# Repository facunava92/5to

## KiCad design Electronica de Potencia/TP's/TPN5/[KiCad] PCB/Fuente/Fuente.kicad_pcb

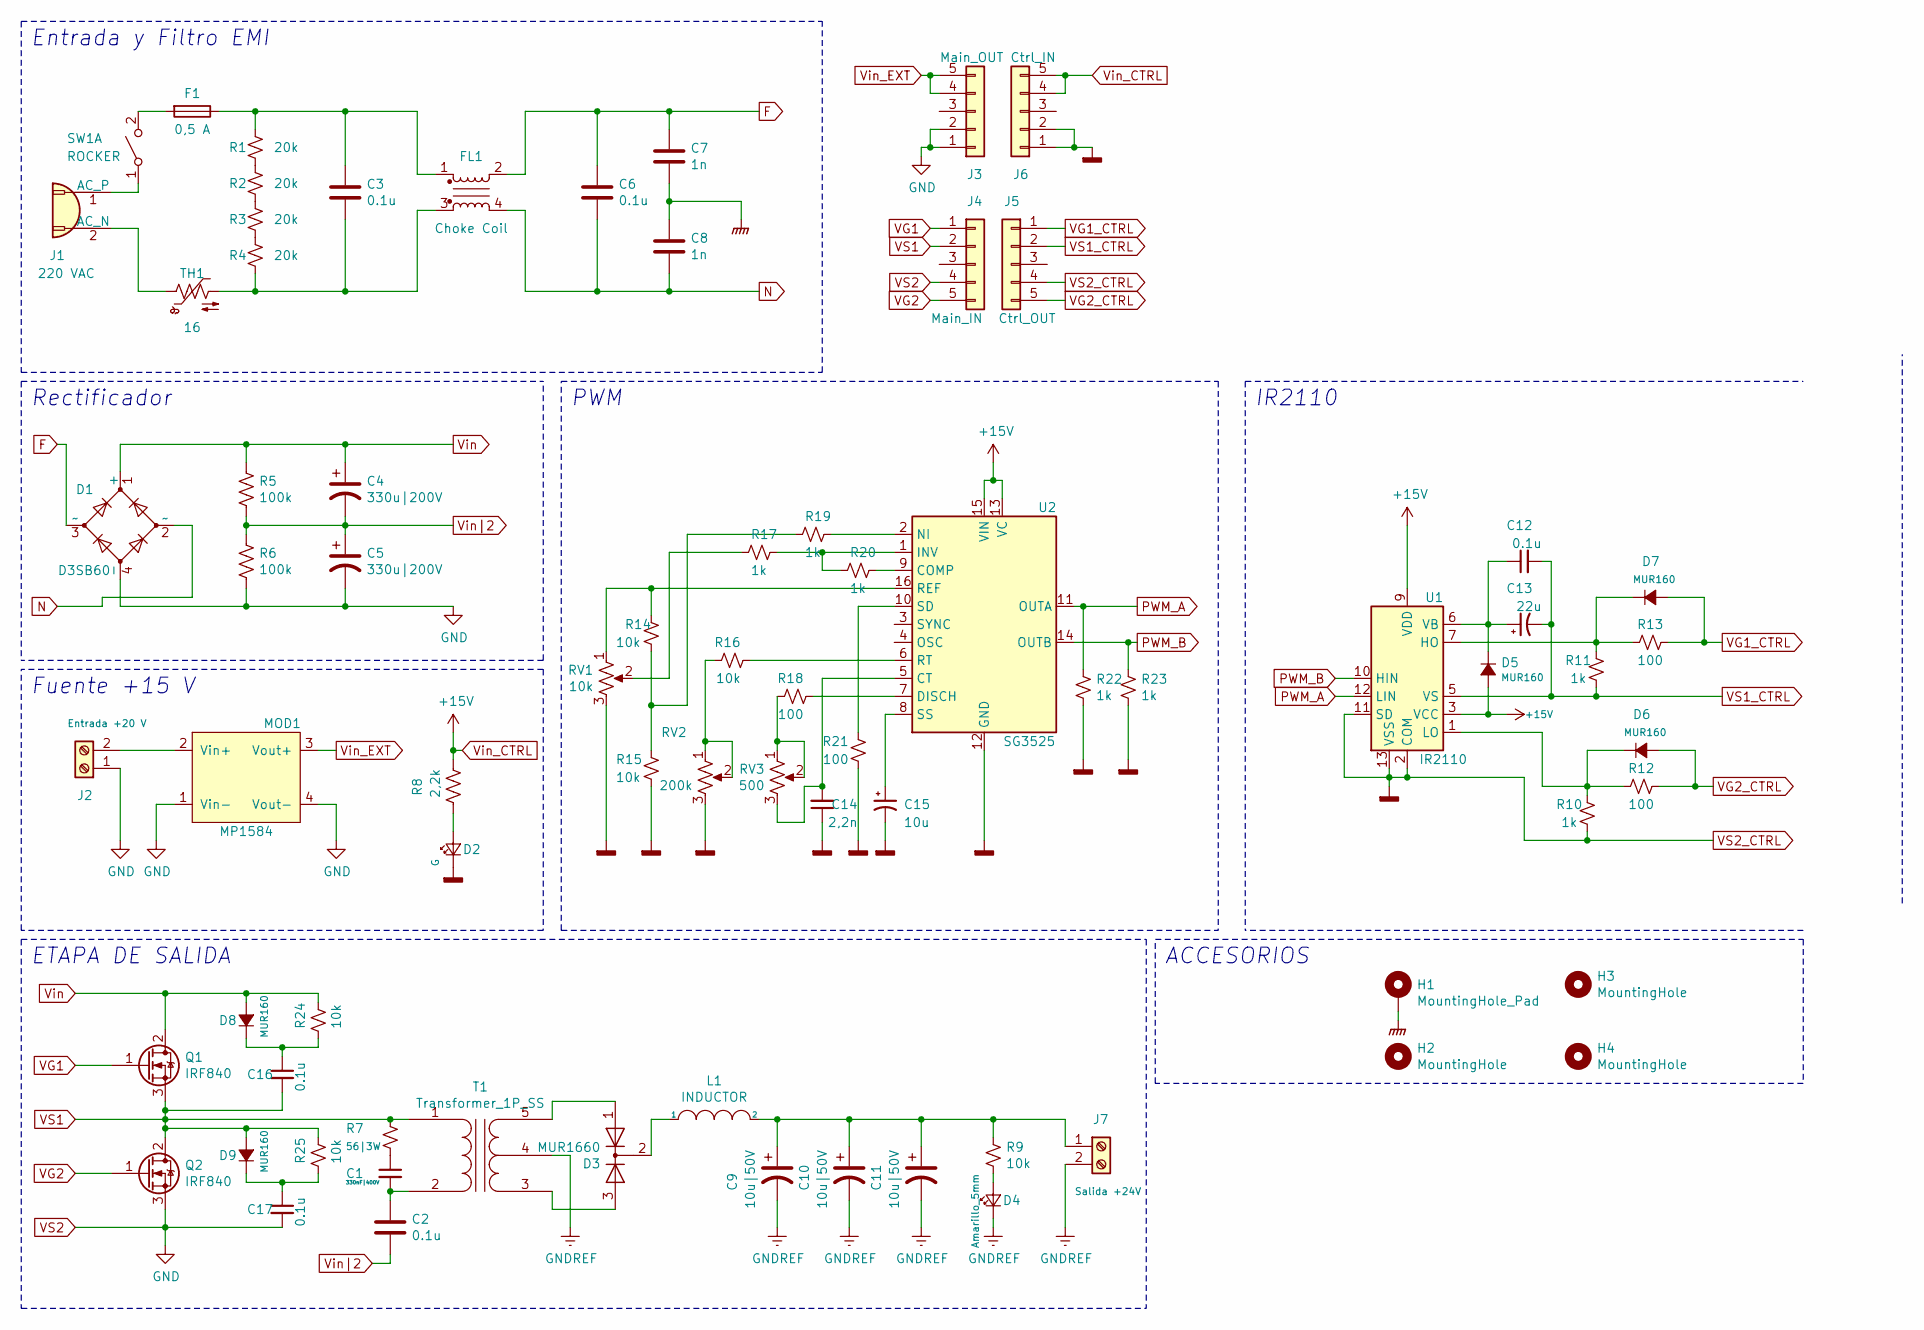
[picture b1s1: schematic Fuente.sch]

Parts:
C1: 330nF|400V; C_Rect_L16.5mm_W5.0mm_P15.00mm_MKT
C2, C3, C6: 0.1u; C_Rect_L16.5mm_W5.0mm_P15.00mm_MKT
C4, C5: 330u|200V; CP_Radial_D25.0mm_P10.00mm_SnapIn
C7, C8: 1n; C_EMI
C9, C10, C11: 10u|50V; CP_Radial_D5.0mm_P2.50mm
C12, C16, C17: 0.1u; C_Disc_D3.8mm_W2.6mm_P2.50mm
C13: 22u; CP_Radial_D5.0mm_P2.50mm
C14: 2,2n; C_Disc_D3.8mm_W2.6mm_P2.50mm
C15: 10u; CP_Radial_D5.0mm_P2.50mm
D1: D3SB60; DS3B
D2: G; LED_D5.0mm_Clear
D3: MUR1660; TO-220-3_Vertical
D4: Amarillo_5mm; LED_D5.0mm_Clear
D5, D6, D7, D8, D9: MUR160; D_DO-41_SOD81_P10.16mm_Horizontal
F1: 0,5 A; Fuse_4pin_A
FL1: Choke Coil; Choke_A
H1: MountingHole_Pad; MountingHole_3.2mm_M3_DIN965_Pad
H2, H3, H4: MountingHole; MountingHole_3.2mm_M3_DIN965
J1: 220 VAC; IEC-C8
J2: Entrada +20 V; TerminalBlock_bornier-2_P5.08mm
J3: Main_OUT; PinSocket_1x05_P2.54mm_Vertical
J4: Main_IN; PinSocket_1x05_P2.54mm_Vertical
J5: Ctrl_OUT; PinHeader_1x05_P2.54mm_Vertical
J6: Ctrl_IN; PinHeader_1x05_P2.54mm_Vertical
J7: Salida +24V; TerminalBlock_bornier-2_P5.08mm
L1: INDUCTOR; L_Toroid_Vertical_L22.4mm_W10.2mm_P7.90mm_Vishay_TJ4
MOD1: MP1584
Q1, Q2: IRF840; TO-220-3_Vertical
R1, R2, R3, R4: 20k; R_0805_2012Metric_Pad1.15x1.40mm_HandSolder
R5, R6: 100k; R_Axial_DIN0207_L6.3mm_D2.5mm_P10.16mm_Horizontal
R7: 56|3W; R_Axial_DIN0617_L17.0mm_D6.0mm_P20.32mm_Horizontal
R8: 2,2k; R_Axial_DIN0207_L6.3mm_D2.5mm_P10.16mm_Horizontal
R9, R14, R15, R16, R24, R25: 10k; R_Axial_DIN0207_L6.3mm_D2.5mm_P10.16mm_Horizontal
R10, R11, R17, R19, R20, R22, R23: 1k; R_Axial_DIN0207_L6.3mm_D2.5mm_P10.16mm_Horizontal
R12, R13, R21: 100; R_Axial_DIN0207_L6.3mm_D2.5mm_P10.16mm_Horizontal
R18: 100; R_Axial_DIN0204_L3.6mm_D1.6mm_P5.08mm_Horizontal
RV1: 10k; Potentiometer_Bourns_3266Y_Vertical
RV2: 200k; Potentiometer_Bourns_3266Y_Vertical
RV3: 500; Potentiometer_Bourns_3266Y_Vertical
SW1: ROCKER; Rocker
T1: Transformer_1P_SS; Transformador_EE25
TH1: 16; NTC-16
U1: IR2110; DIP-14_W7.62mm_LongPads
U2: SG3525; DIP-16_W7.62mm_LongPads

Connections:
F: C6.1, C7.1, D1.3 (~~), FL1.2
GNDPWR: C7.2, C8.1, H1.1
GNDREF: C9.2, C10.2, C11.2, D4.1 (K), J7.2, T1.4 (SC)
N: C6.2, C8.2, D1.2 (~~), FL1.4
unnamed: C1.1, R7.2
unnamed: C1.2, C2.1, T1.2 (AB)
unnamed: C3.1, F1.1, FL1.1, R1.1
unnamed: C3.2, FL1.3, R4.2, TH1.2
unnamed: C9.1, C10.1, C11.1, J7.1, L1.2, R9.1
unnamed: C12.1, C13.1, D5.1 (K), U1.6 (VB)
unnamed: C14.2, RV3.3, U2.5 (CT)
unnamed: C15.1, U2.8 (SS)
unnamed: C16.1, D8.1 (K), R24.2
unnamed: C17.1, D9.1 (K), R25.2
unnamed: D2.2 (A), R8.1
unnamed: D3.1 (A), T1.5 (SB)
unnamed: D3.2 (K), L1.1
unnamed: D3.3 (A), T1.3 (SA)
unnamed: D4.2 (A), R9.2
unnamed: D6.1 (K), R10.2, R12.1, U1.1 (LO)
unnamed: D7.1 (K), R11.2, R13.1, U1.7 (HO)
unnamed: F1.2, SW1.2 (B)
unnamed: J1.1 (AC_P), SW1.1 (A)
unnamed: J1.2 (AC_N), TH1.1
unnamed: J2.2, MOD1.2 (Vin+)
unnamed: R1.2, R2.1
unnamed: R2.2, R3.1
unnamed: R3.2, R4.1
unnamed: R14.1, RV1.1, U2.16 (REF)
unnamed: R14.2, R15.1, R19.2
unnamed: R16.1, RV2.1, RV2.2
unnamed: R16.2, U2.6 (RT)
unnamed: R17.1, R20.2, U2.1 (INV)
unnamed: R17.2, RV1.2
unnamed: R18.1, RV3.1, RV3.2
unnamed: R18.2, U2.7 (DISCH)
unnamed: R19.1, U2.2 (NI)
unnamed: R20.1, U2.9 (COMP)
unnamed: R21.2, U2.10 (SD)
PWM_A: R22.1, U1.12 (LIN), U2.11 (OUTA)
PWM_B: R23.1, U1.10 (HIN), U2.14 (OUTB)
VG1: J4.1, Q1.1 (G)
VG1_CTRL: D7.2 (A), J5.1, R13.2
VG2: J4.5, Q2.1 (G)
VG2_CTRL: D6.2 (A), J5.5, R12.2
VS1: C16.2, D9.2 (A), J4.2, Q1.3 (S), Q2.2 (D), R7.1, R25.1, T1.1 (AA)
VS1_CTRL: C12.2, C13.2, J5.2, R11.1, U1.5 (VS)
VS2: C5.2, C17.2, D1.4 (-), J2.1, J3.1, J3.2, J4.4, MOD1.1 (Vin-), MOD1.4 (Vout-), Q2.3 (S), R6.2
VS2_CTRL: C14.1, C15.2, D2.1 (K), J5.4, J6.1, J6.2, R10.1, R15.2, R21.1, R22.2, R23.2, RV1.3, RV2.3, U1.2 (COM), U1.11 (SD), U1.13 (VSS), U2.12 (GND)
Vin: C4.1, D1.1 (+), D8.2 (A), Q1.2 (D), R5.1, R24.1
Vin_CTRL: D5.2 (A), J6.4, J6.5, R8.2, U1.3 (VCC), U1.9 (VDD), U2.13 (VC), U2.15 (VIN)
Vin_EXT: J3.4, J3.5, MOD1.3 (Vout+)
Vin|2: C2.2, C4.2, C5.1, R5.2, R6.1

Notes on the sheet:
Entrada y Filtro EMI
Rectificador
Fuente +15 V
PWM
IR2110
ETAPA DE SALIDA
ACCESORIOS

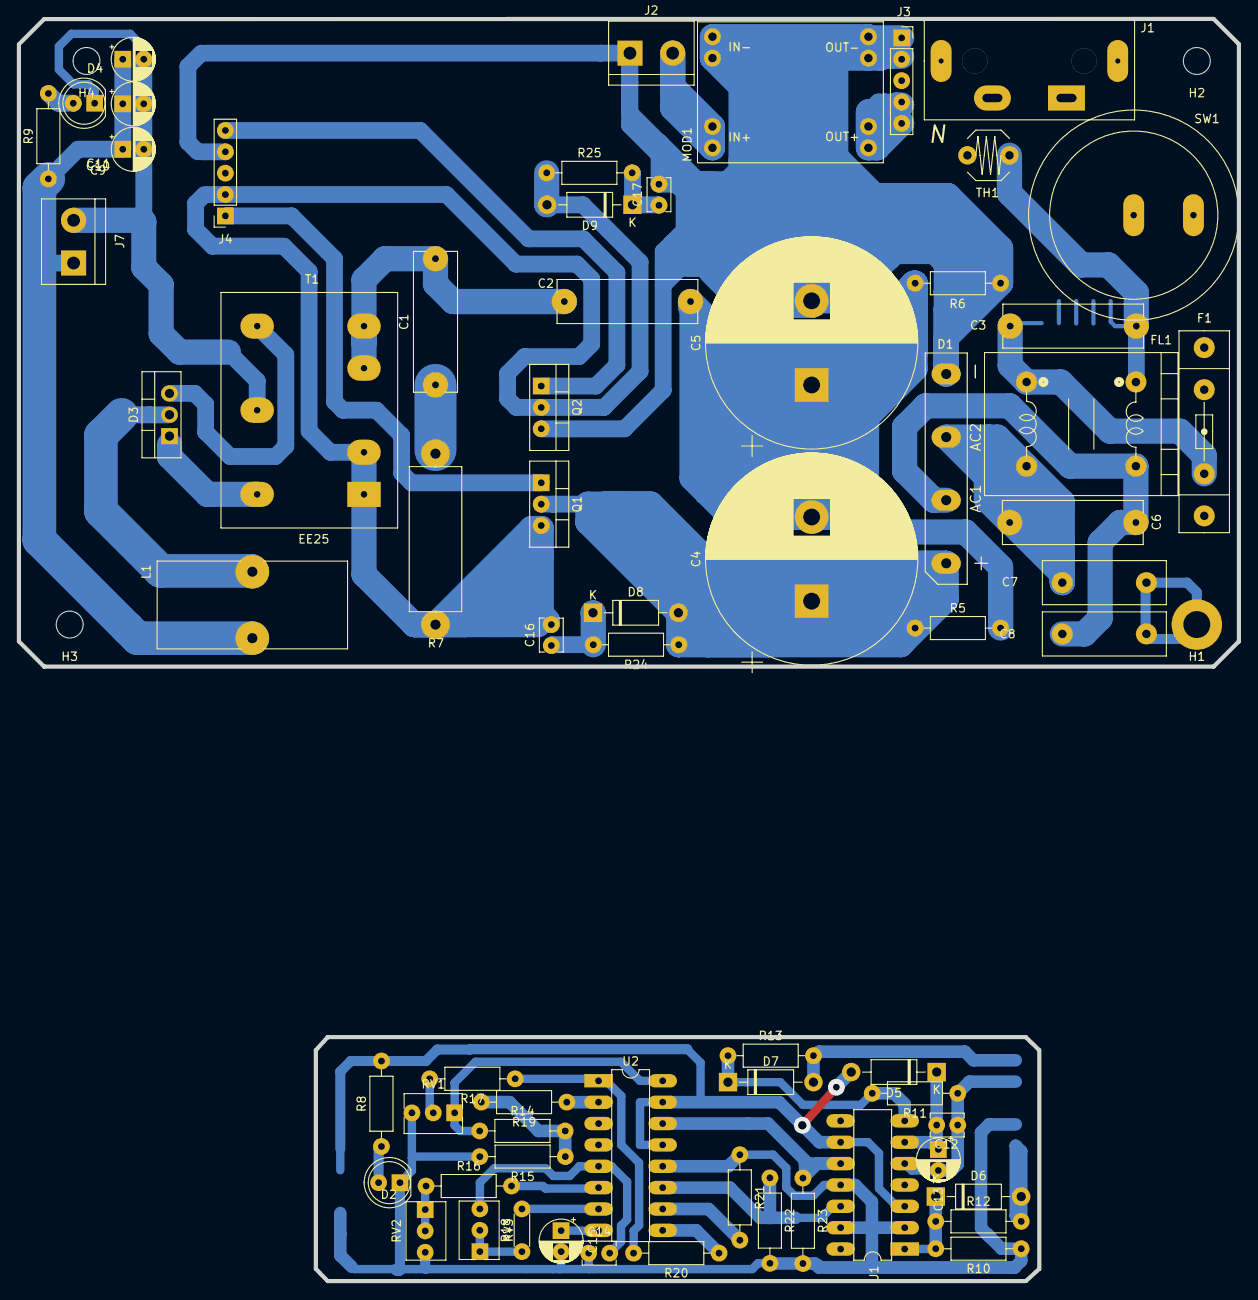
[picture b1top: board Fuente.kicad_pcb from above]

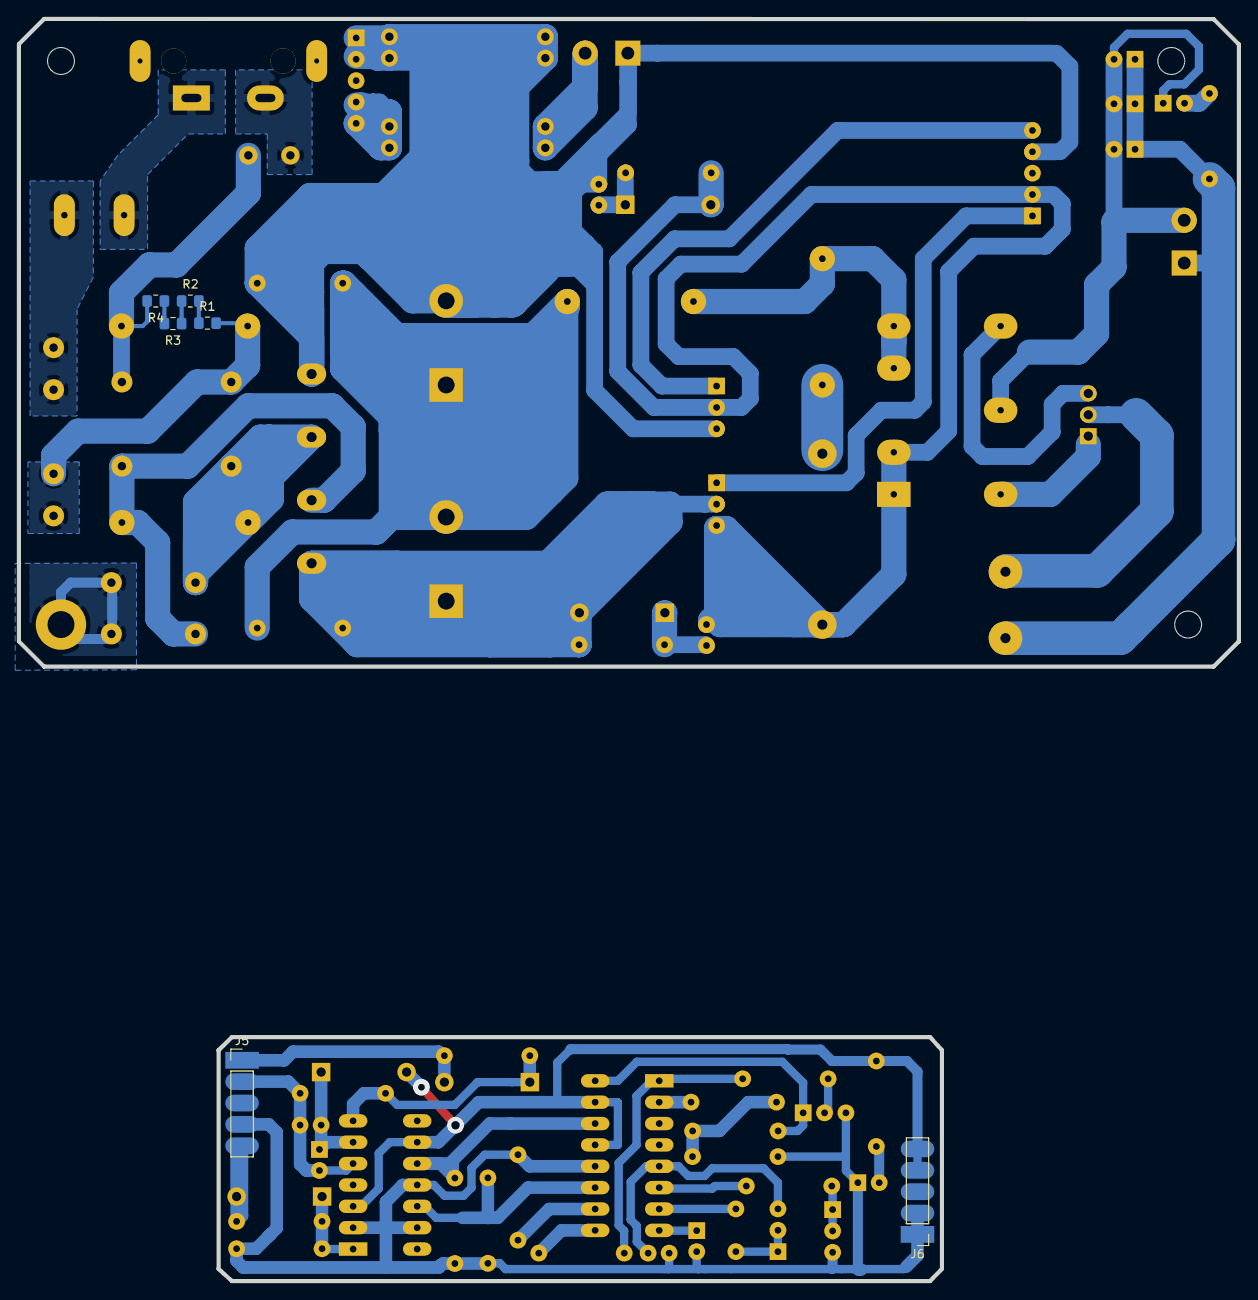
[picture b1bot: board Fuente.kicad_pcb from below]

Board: 2 copper layers, 145.0 x 150.1 mm, 76 parts (6 on the bottom side), 53 nets.

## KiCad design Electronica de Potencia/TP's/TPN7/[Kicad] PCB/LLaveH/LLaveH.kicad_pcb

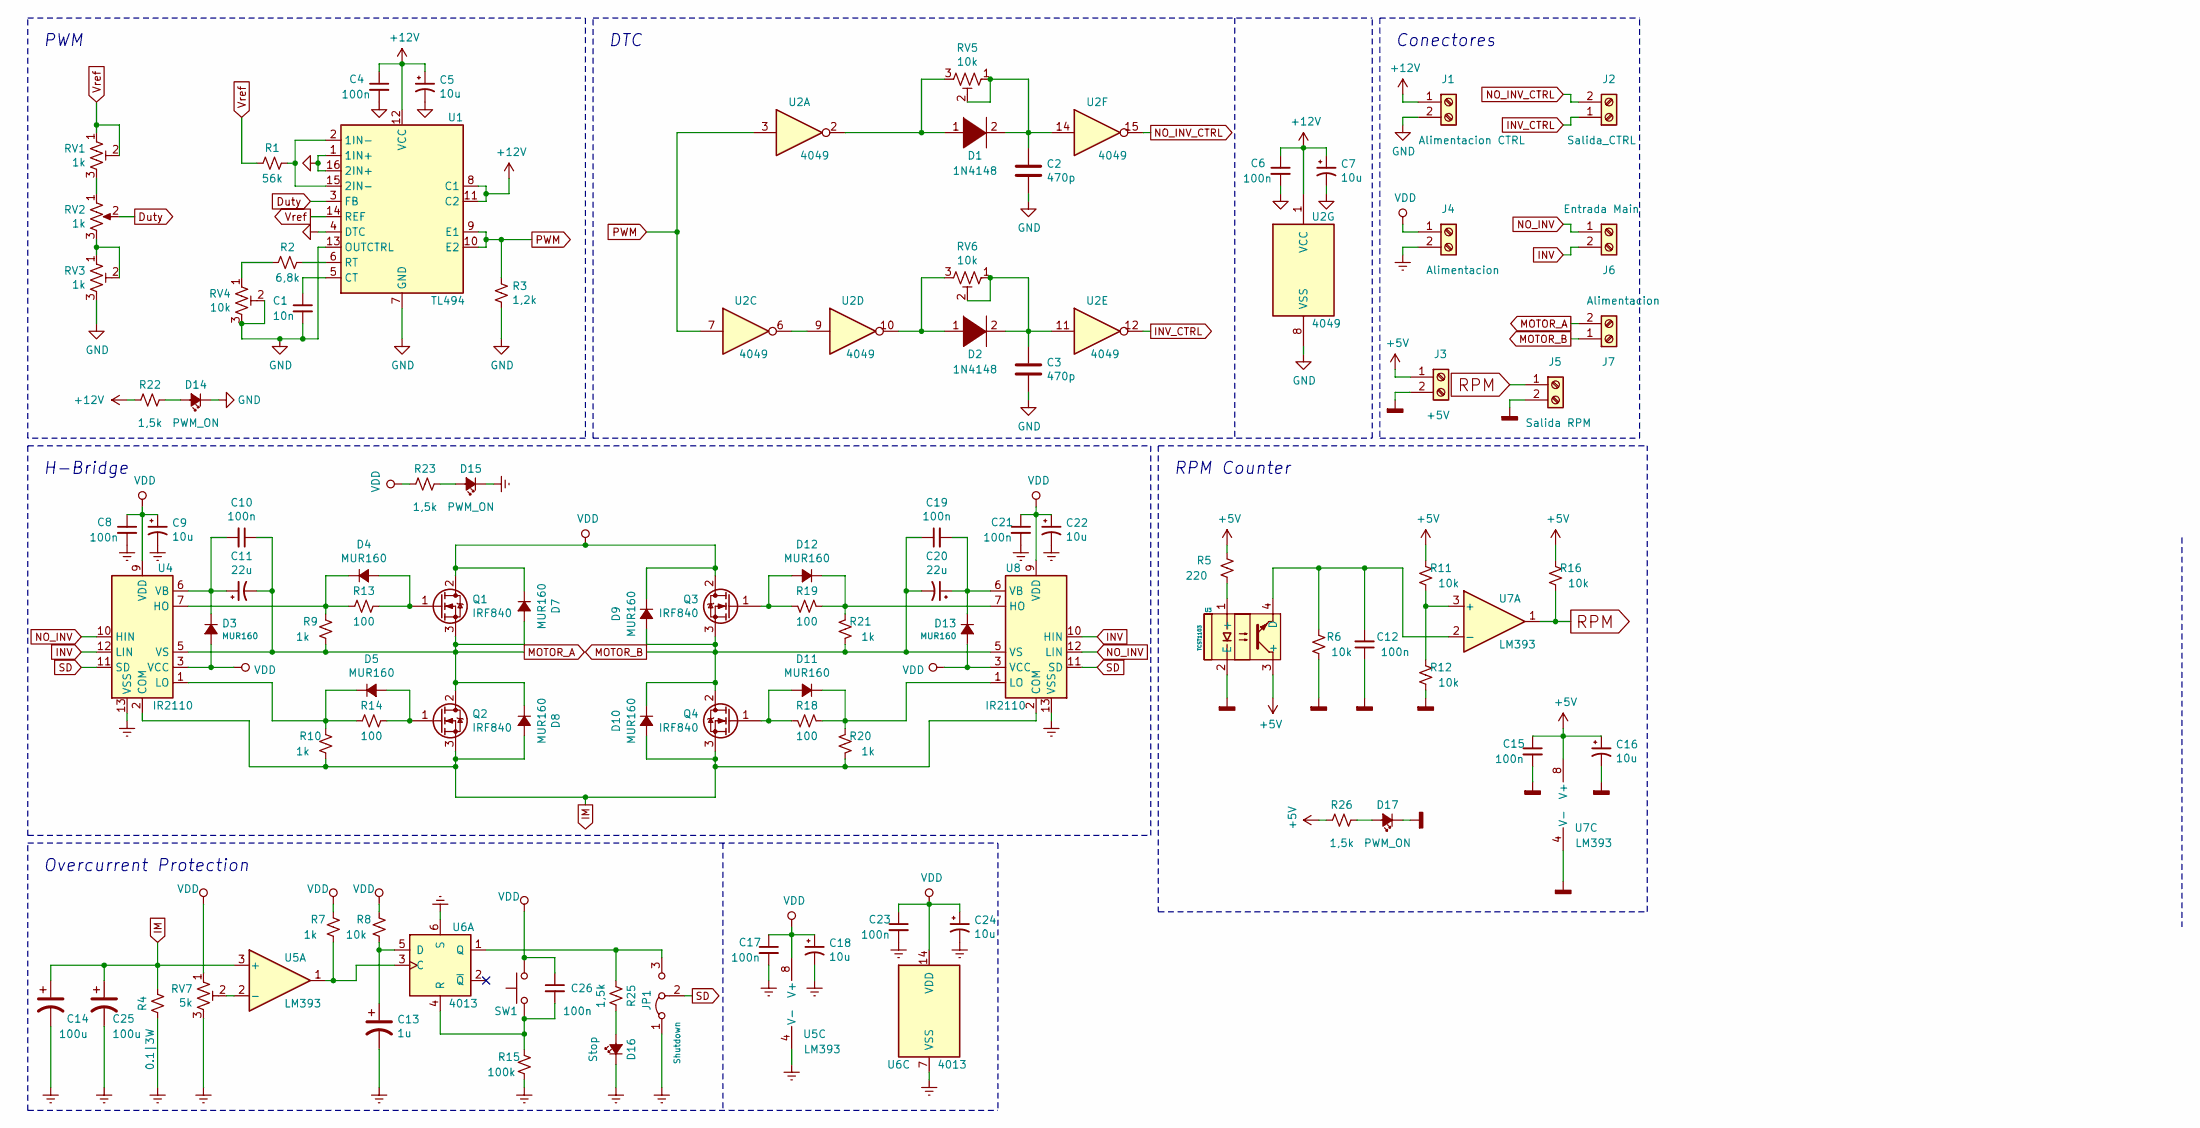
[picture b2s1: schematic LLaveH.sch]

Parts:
C1: 10n; C_Disc_D3.8mm_W2.6mm_P2.50mm
C2, C3: 470p; C_Disc_D3.8mm_W2.6mm_P2.50mm
C4, C6, C8, C10, C12, C15, C17, C19, C21, C23, C26: 100n; C_Disc_D3.8mm_W2.6mm_P2.50mm
C5, C7, C9, C16, C18, C22, C24: 10u; CP_Radial_D5.0mm_P2.50mm
C11, C20: 22u; CP_Radial_D5.0mm_P2.50mm
C13: 1u; CP_Radial_D5.0mm_P2.50mm
C14, C25: 100u; CP_Radial_D8.0mm_P3.80mm
D1, D2: 1N4148; D_DO-34_SOD68_P7.62mm_Horizontal
D3, D4, D5, D7, D8, D9, D10, D11, D12, D13: MUR160; D_DO-41_SOD81_P10.16mm_Horizontal
D14, D15, D17: PWM_ON; LED_D5.0mm_Clear
D16: Stop; LED_D5.0mm_Clear
J1: Alimentacion CTRL; TerminalBlock_screwless-2_P5mm
J2: Salida_CTRL; TerminalBlock_screwless-2_P5mm
J3: +5V; TerminalBlock_screwless-2_P5mm
J4, J7: Alimentacion; TerminalBlock_screwless-2_P5mm
J5: Salida RPM; TerminalBlock_screwless-2_P5mm
J6: Entrada Main; TerminalBlock_screwless-2_P5mm
JP1: Shutdown; PinHeader_1x03_P2.54mm_Vertical
Q1, Q2, Q3, Q4: IRF840; TO-220-3_Vertical
R1: 56k; R_Axial_DIN0207_L6.3mm_D2.5mm_P10.16mm_Horizontal
R2: 6,8k; R_Axial_DIN0207_L6.3mm_D2.5mm_P10.16mm_Horizontal
R3: 1,2k; R_Axial_DIN0207_L6.3mm_D2.5mm_P10.16mm_Horizontal
R4: 0.1|3W; R_Axial_DIN0617_L17.0mm_D6.0mm_P20.32mm_Horizontal
R5: 220; R_Axial_DIN0207_L6.3mm_D2.5mm_P10.16mm_Horizontal
R6, R8, R11, R12, R16: 10k; R_Axial_DIN0207_L6.3mm_D2.5mm_P10.16mm_Horizontal
R7, R9, R10, R20, R21: 1k; R_Axial_DIN0207_L6.3mm_D2.5mm_P10.16mm_Horizontal
R13, R14, R18, R19: 100; R_Axial_DIN0207_L6.3mm_D2.5mm_P10.16mm_Horizontal
R15: 100k; R_Axial_DIN0207_L6.3mm_D2.5mm_P10.16mm_Horizontal
R22, R23, R25, R26: 1,5k; R_Axial_DIN0207_L6.3mm_D2.5mm_P10.16mm_Horizontal
RV1, RV3: 1k; Potentiometer_Bourns_3266Y_Vertical
RV2: 1k; Potentiometer_Alps_RK163_Single_Horizontal
RV4, RV5, RV6: 10k; Potentiometer_Bourns_3266Y_Vertical
RV7: 5k; Potentiometer_Bourns_3266Y_Vertical
SW1: SW_Push; SW_PUSH_6mm_H5mm
U1: TL494; DIP-16_W7.62mm_LongPads
U2: 4049; DIP-16_W7.62mm_LongPads
U3: TCST1103
U4, U8: IR2110; DIP-14_W7.62mm_LongPads
U5, U7: LM393; DIP-8_W7.62mm_LongPads
U6: 4013; DIP-14_W7.62mm_LongPads

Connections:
+5V: C15.1, C16.1, J3.1, R5.2, R11.2, R16.2, R26.2, U3.3 (+), U7.8 (V+)
+12V: C4.1, C5.1, C6.1, C7.1, J1.1, R22.2, U1.8 (C1), U1.11 (C2), U1.12 (VCC), U2.1 (VCC)
Duty: RV2.2, U1.3 (FB)
Earth: C8.2, C9.2, C13.2, C14.2, C17.2, C18.2, C21.2, C22.2, C23.2, C24.2, C25.2, D15.1 (K), D16.1 (K), J4.2, JP1.1 (A), R4.1, R15.1, RV7.3, U4.13 (VSS), U5.4 (V-), U6.6 (S), U6.7 (VSS), U8.13 (VSS)
GND: C1.2, C2.2, C3.2, C4.2, C5.2, C6.2, C7.2, D14.1 (K), J1.2, R3.2, RV3.3, RV4.2, RV4.3, U1.1 (1IN+), U1.4 (DTC), U1.7 (GND), U1.13 (OUTCTRL), U1.16 (2IN+), U2.8 (VSS)
GNDD: C12.1, C15.2, C16.2, D17.1 (K), J3.2, J5.2, R6.1, R12.1, U3.2 (E), U7.4 (V-)
IM: C14.1, C25.1, D8.2 (A), D10.2 (A), Q2.3 (S), Q4.3 (S), R4.2, R10.1, R20.1, U4.2 (COM), U5.3 (+), U8.2 (COM)
INV: J6.2, U4.12 (LIN), U8.10 (HIN)
INV_CTRL: J2.1, U2.12
MOTOR_A: C10.1, C11.2, D7.2 (A), D8.1 (K), J7.2, Q1.3 (S), Q2.2 (D), R9.1, U4.5 (VS)
MOTOR_B: C19.1, C20.2, D9.2 (A), D10.1 (K), J7.1, Q3.3 (S), Q4.2 (D), R21.1, U8.5 (VS)
NO_INV: J6.1, U4.10 (HIN), U8.12 (LIN)
NO_INV_CTRL: J2.2, U2.15
unnamed: C1.1, U1.5 (CT)
unnamed: C2.1, D1.2 (A), RV5.1, RV5.2, U2.14
unnamed: C3.1, D2.2 (A), RV6.1, RV6.2, U2.11
unnamed: C10.2, C11.1, D3.1 (K), U4.6 (VB)
unnamed: C12.2, R6.2, U3.4 (D), U7.2 (-)
unnamed: C13.1, R8.1, U6.5 (D)
unnamed: C19.2, C20.1, D13.1 (K), U8.6 (VB)
unnamed: C26.2, R15.2, SW1.1, U6.4 (R)
unnamed: D1.1 (K), RV5.3, U2.2
unnamed: D2.1 (K), RV6.3, U2.10
unnamed: D4.1 (K), R9.2, R13.2, U4.7 (HO)
unnamed: D4.2 (A), Q1.1 (G), R13.1
unnamed: D5.1 (K), R10.2, R14.2, U4.1 (LO)
unnamed: D5.2 (A), Q2.1 (G), R14.1
unnamed: D11.1 (K), R18.2, R20.2, U8.1 (LO)
unnamed: D11.2 (A), Q4.1 (G), R18.1
unnamed: D12.1 (K), R19.2, R21.2, U8.7 (HO)
unnamed: D12.2 (A), Q3.1 (G), R19.1
unnamed: D14.2 (A), R22.1
unnamed: D15.2 (A), R23.1
unnamed: D16.2 (A), R25.1
unnamed: D17.2 (A), R26.1
unnamed: JP1.3 (B), R25.2, U6.1 (Q)
unnamed: R1.1, U1.2 (1IN-), U1.15 (2IN-)
unnamed: R2.1, U1.6 (RT)
unnamed: R2.2, RV4.1
unnamed: R5.1, U3.1 (+)
unnamed: R7.1, U5.1, U6.3 (C)
unnamed: R11.1, R12.2, U7.3 (+)
unnamed: RV1.3, RV2.1
unnamed: RV2.3, RV3.1, RV3.2
unnamed: RV7.2, U5.2 (-)
unnamed: U2.6, U2.9
PWM: R3.1, U1.9 (E1), U1.10 (E2), U2.3, U2.7
RPM: J5.1, R16.1, U7.1
SD: JP1.2 (C), U4.11 (SD), U8.11 (SD)
VDD: C8.1, C9.1, C17.1, C18.1, C21.1, C22.1, C23.1, C24.1, C26.1, D3.2 (A), D7.1 (K), D9.1 (K), D13.2 (A), J4.1, Q1.2 (D), Q3.2 (D), R7.2, R8.2, R23.2, RV7.1, SW1.2, U4.3 (VCC), U4.9 (VDD), U5.8 (V+), U6.14 (VDD), U8.3 (VCC), U8.9 (VDD)
Vref: R1.2, RV1.1, RV1.2, U1.14 (REF)

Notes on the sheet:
PWM
DTC
Conectores
H-Bridge
Overcurrent Protection
RPM Counter

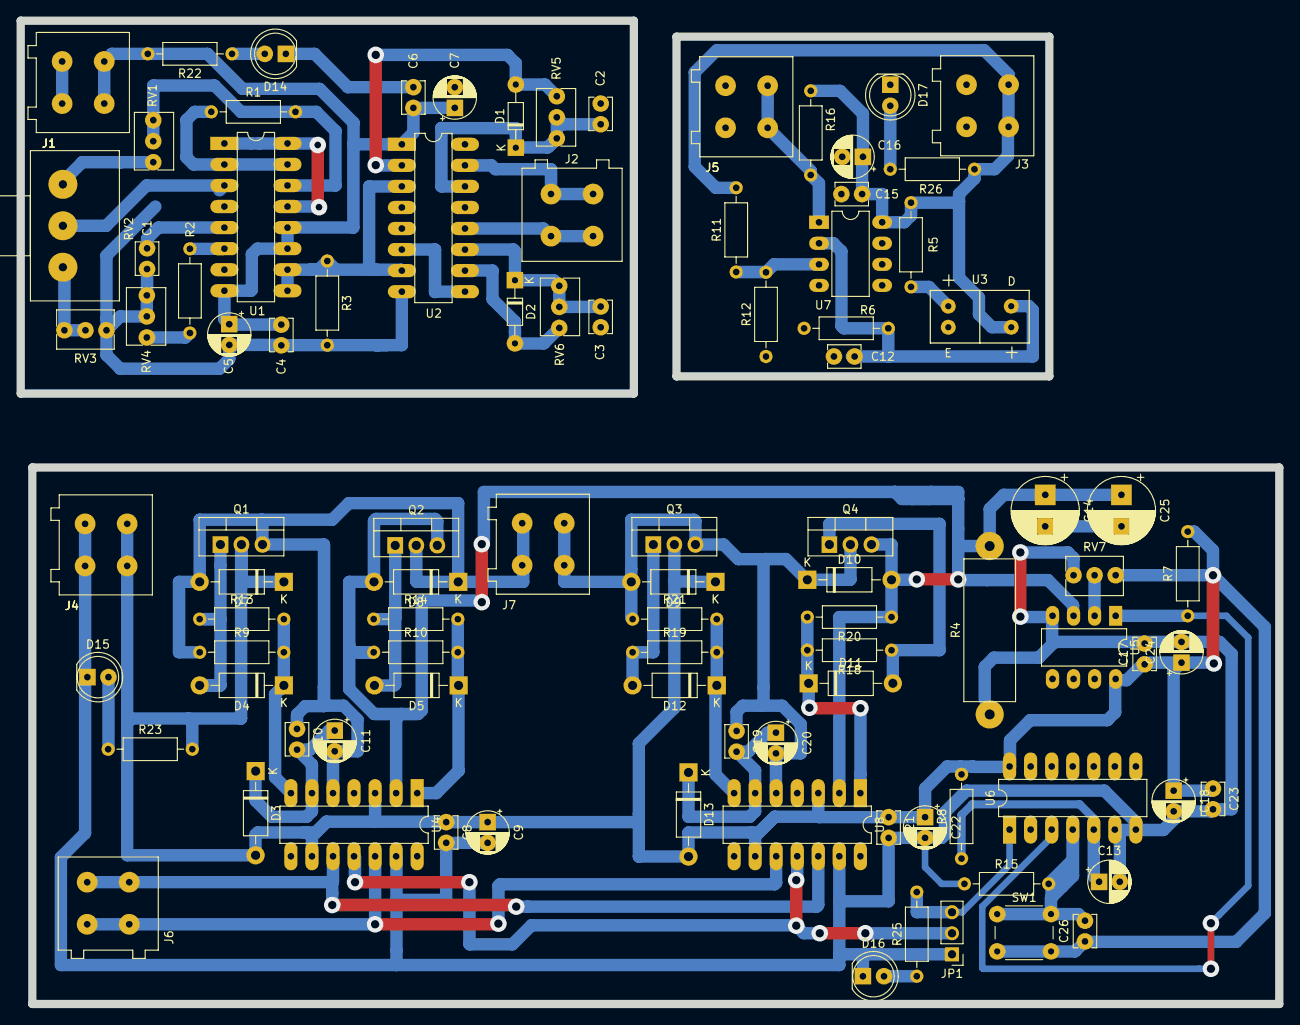
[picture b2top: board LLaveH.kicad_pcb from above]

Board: 2 copper layers, 151.9 x 118.7 mm, 94 parts (0 on the bottom side), 51 nets.

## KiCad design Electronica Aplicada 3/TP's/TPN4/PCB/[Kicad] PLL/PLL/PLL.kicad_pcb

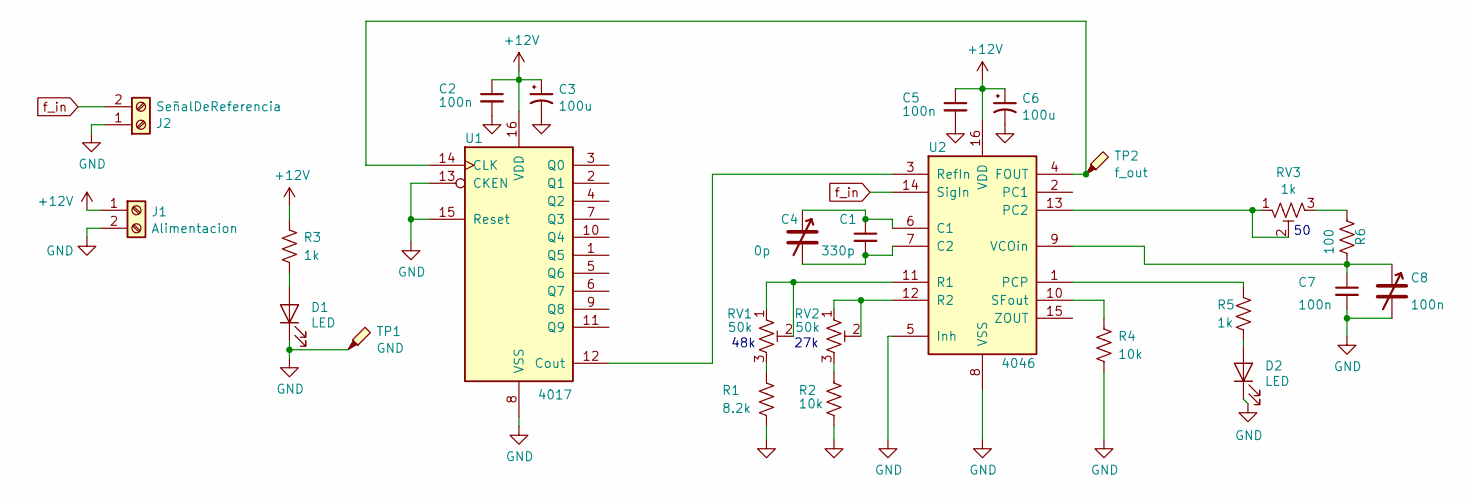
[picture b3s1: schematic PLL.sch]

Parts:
C1: 330p; C_Disc_D5.0mm_W2.5mm_P2.50mm
C2, C5, C7: 100n; C_Disc_D5.0mm_W2.5mm_P2.50mm
C3, C6: 100u; C_Radial_D5.0mm_H11.0mm_P2.00mm
C4: 0p; TrimmerCapacitor
C8: 100n; TrimmerCapacitor
D1, D2: LED; LED_D3.0mm_Clear
J1: Alimentacion; TerminalBlock_bornier-2_P5.08mm
J2: SeñalDeReferencia; TerminalBlock_bornier-2_P5.08mm
R1: 8.2k; R_Axial_DIN0207_L6.3mm_D2.5mm_P10.16mm_Horizontal
R2, R4: 10k; R_Axial_DIN0207_L6.3mm_D2.5mm_P10.16mm_Horizontal
R3, R5: 1k; R_Axial_DIN0207_L6.3mm_D2.5mm_P10.16mm_Horizontal
R6: 100; R_Axial_DIN0207_L6.3mm_D2.5mm_P10.16mm_Horizontal
RV1, RV2: 50k; Potentiometer_Bourns_3266Y_Vertical
RV3: 1k; Potentiometer_Bourns_3266Y_Vertical
TP1: GND; Testpoint
TP2: f_out; Testpoint
U1: 4017; DIP-16_W7.62mm_LongPads
U2: 4046; DIP-16_W7.62mm_LongPads

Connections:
+12V: C2.1, C3.1, C5.1, C6.1, J1.1, R3.1, U1.16 (VDD), U2.16 (VDD)
GND: C2.2, C3.2, C5.2, C6.2, C7.2, C8.2, D1.1 (K), D2.1 (K), J1.2, J2.1, R1.2, R2.2, R4.2, TP1.1, U1.8 (VSS), U1.13 (CKEN), U1.15 (Reset), U2.5 (Inh), U2.8 (VSS)
unnamed: C1.1, C4.1, U2.6 (C1)
unnamed: C1.2, C4.2, U2.7 (C2)
unnamed: C7.1, C8.1, R6.2, U2.9 (VCOin)
unnamed: D1.2 (A), R3.2
unnamed: D2.2 (A), R5.2
unnamed: R1.1, RV1.3
unnamed: R2.1, RV2.3
unnamed: R4.1, U2.10 (SFout)
unnamed: R5.1, U2.1 (PCP)
unnamed: R6.1, RV3.3
unnamed: RV1.1, RV1.2, U2.11 (R1)
unnamed: RV2.1, RV2.2, U2.12 (R2)
unnamed: RV3.1, RV3.2, U2.13 (PC2)
unnamed: TP2.1, U1.14 (CLK), U2.4 (FOUT)
unnamed: U1.12 (Cout), U2.3 (RefIn)
f_in: J2.2, U2.14 (SigIn)

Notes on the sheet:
48k
27k

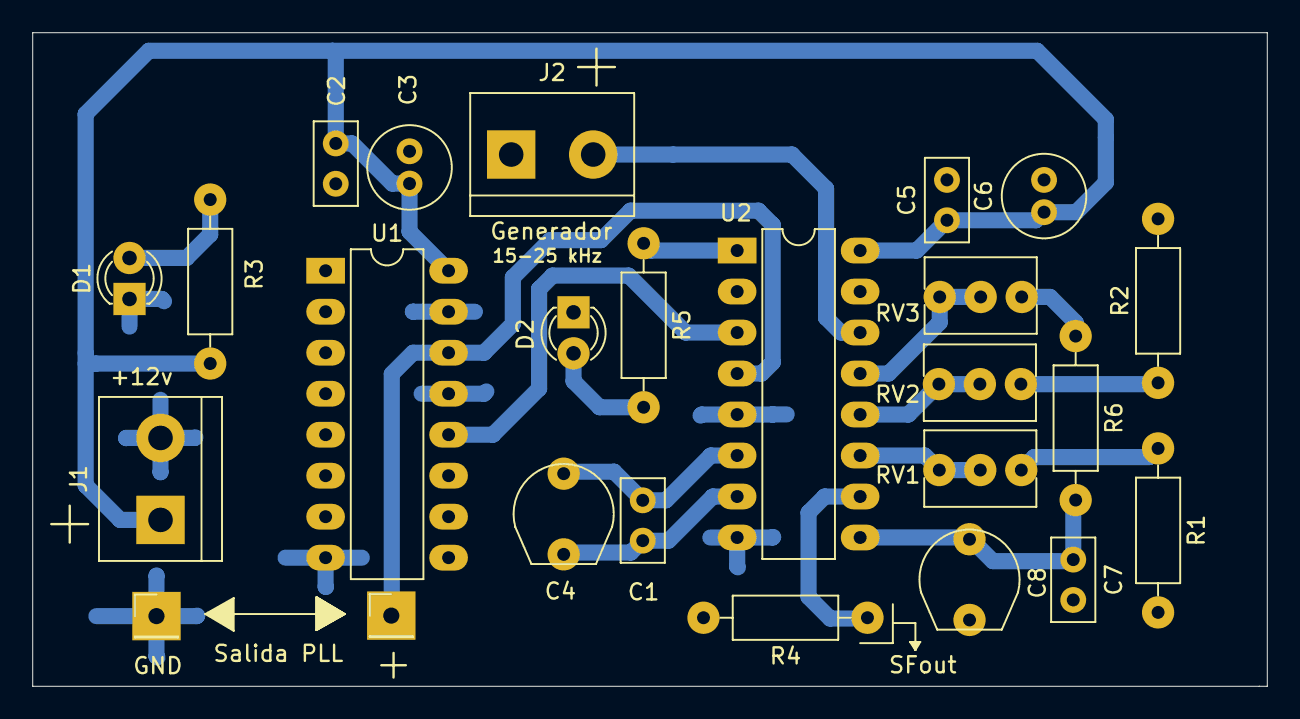
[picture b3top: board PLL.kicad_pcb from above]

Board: 2 copper layers, 76.5 x 40.5 mm, 25 parts (0 on the bottom side), 18 nets.

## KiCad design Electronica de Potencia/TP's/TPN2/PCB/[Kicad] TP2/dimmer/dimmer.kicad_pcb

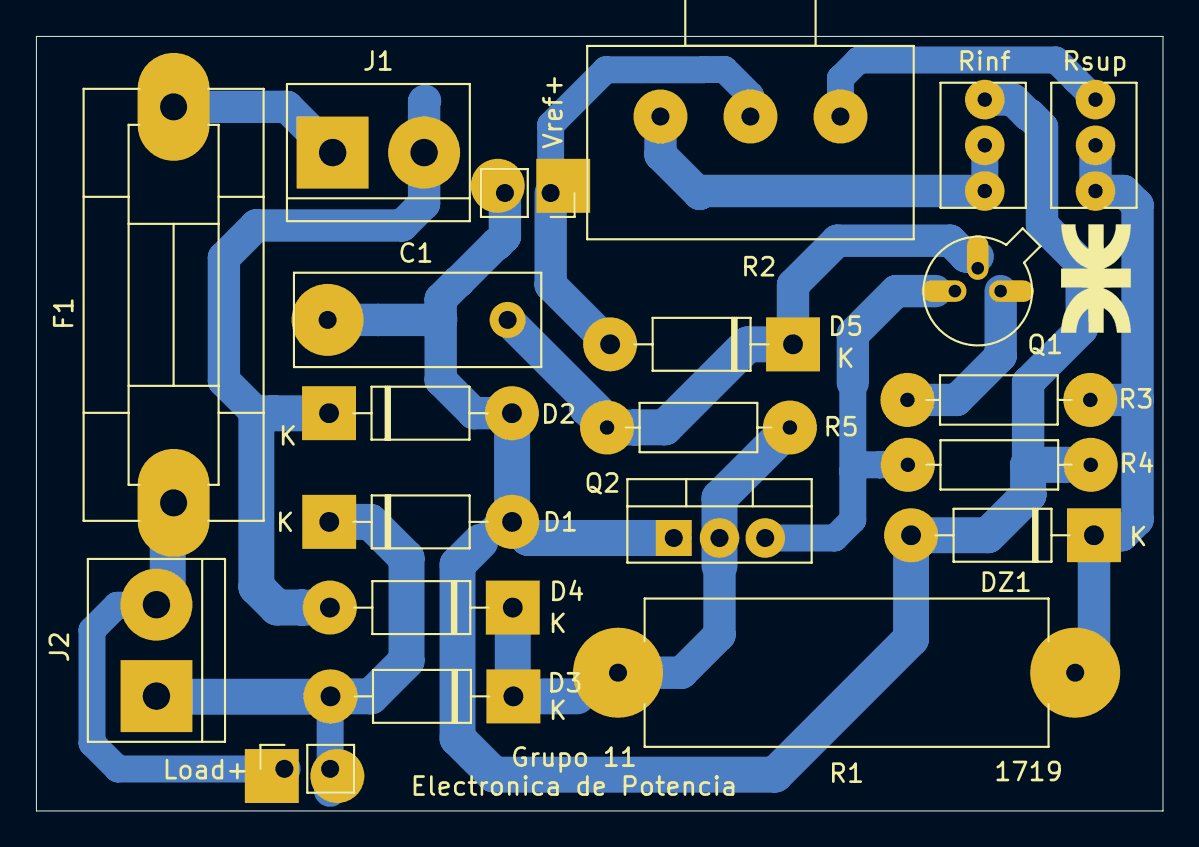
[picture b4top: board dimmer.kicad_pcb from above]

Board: 2 copper layers, 62.6 x 43.0 mm, 22 parts (0 on the bottom side), 13 nets.

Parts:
C1: 0,1uF 400V; C_Rect_L13.5mm_W5.0mm_P10.00mm_FKS3_FKP3_MKS4
D1, D2, D3, D4, D5: 1N4007; D_DO-41_SOD81_P10.16mm_Horizontal
DZ1: Diode_1N47xxA; D_DO-41_SOD81_P10.16mm_Horizontal
F1: Fuse; Fuseholder5x20_horiz_SemiClosed_Casing10x25mm
G1: LOGO; logo_utn_fsilk_small
J1: Vin; TerminalBlock_bornier-2_P5.08mm
J2: Vout; TerminalBlock_bornier-2_P5.08mm
Load+: TestPoint_2Pole; PinSocket_1x02_P2.54mm_Vertical
Q1: 2N2647; TO-18-3
Q2: TIC106; TO-220-3_Vertical
R1: 10k_5W; R_Axial_Shunt_L22.2mm_W8.0mm_PS14.30mm_P25.40mm
R2: R_POT; Potentiometer_Alps_RK163_Single_Horizontal
R3: 180; R_Axial_DIN0207_L6.3mm_D2.5mm_P10.16mm_Horizontal
R4: 82; R_Axial_DIN0207_L6.3mm_D2.5mm_P10.16mm_Horizontal
R5: 3,3M; R_Axial_DIN0207_L6.3mm_D2.5mm_P10.16mm_Horizontal
Rinf: R_POT_TRIM; Potentiometer_Bourns_3266Y_Vertical
Rsup: R_POT_TRIM; Potentiometer_Bourns_3266Y_Vertical
Vref+: TestPoint_2Pole; PinSocket_1x02_P2.54mm_Vertical

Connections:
/Load+: F1.2, J2.2, Load+.1
/Load-: D1.1, D3.2, J2.1, Load+.2
/Vref+: D5.2, R2.2, Vref+.1
/Vref-: C1.2, D1.2, D2.2, DZ1.2, Q2.1, R4.2, Rinf.3, Vref+.2
GND: D2.1, D4.2, J1.2
unnamed: C1.1, D5.1, Q1.1, R5.2
unnamed: D3.1, D4.1, Q2.2, R1.1, R5.1
unnamed: DZ1.1, R1.2, R3.1, Rsup.1, Rsup.2
unnamed: F1.1, J1.1
unnamed: Q1.2, Q2.3, R4.1
unnamed: Q1.3, R3.2
unnamed: R2.1, Rsup.3
unnamed: R2.3, Rinf.1, Rinf.2

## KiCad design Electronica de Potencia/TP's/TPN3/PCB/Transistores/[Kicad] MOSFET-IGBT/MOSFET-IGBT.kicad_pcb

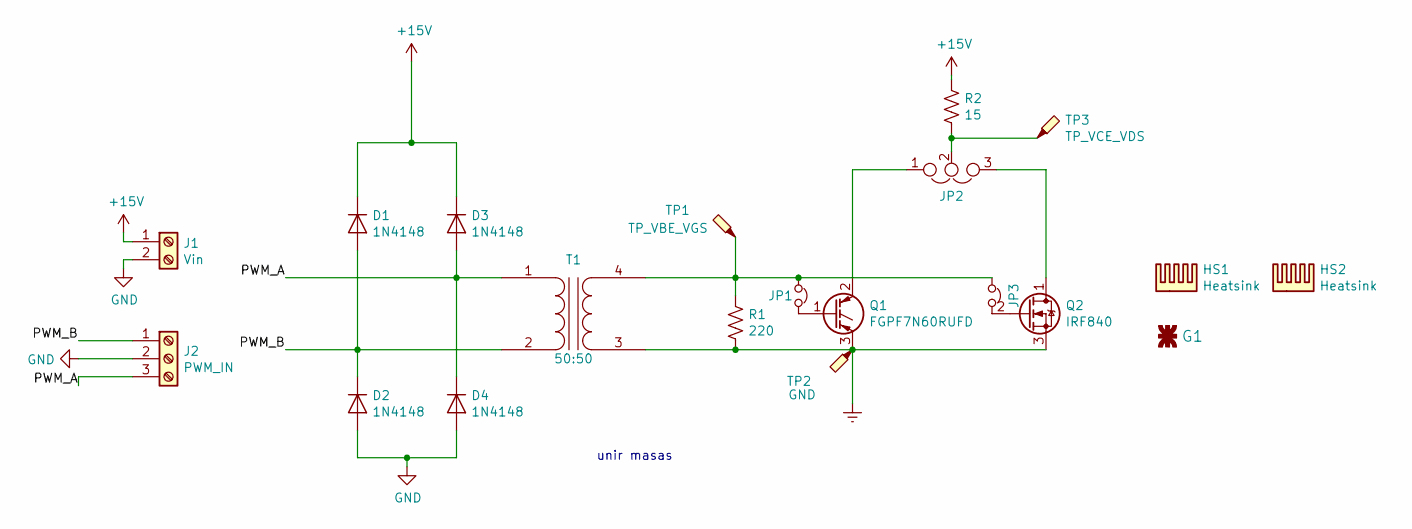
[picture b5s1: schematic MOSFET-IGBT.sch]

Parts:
D1, D2, D3, D4: 1N4148; D_DO-34_SOD68_P7.62mm_Horizontal
G1: logo; logo_utn_fsilk_small
HS1, HS2: Heatsink; Heatsink_TO220_A
J1: Vin; TerminalBlock_bornier-2_P5.08mm
J2: PWM_IN; TerminalBlock_bornier-3_P5.08mm
JP1, JP3: Jumper_NC_Small; PinHeader_1x02_P2.54mm_Vertical
JP2: Jumper_NC_Dual; PinHeader_1x03_P2.54mm_Vertical
Q1: FGPF7N60RUFD; TO-220-3_Vertical
Q2: IRF840; TO-220-3_Vertical
R1: 220; R_Axial_DIN0207_L6.3mm_D2.5mm_P10.16mm_Horizontal
R2: 15; R_Axial_Power_L50.0mm_W9.0mm_P55.88mm
T1: 50:50; Transformador_EE25
TP1: TP_VBE_VGS; Testpoint
TP2: GND; Testpoint
TP3: TP_VCE_VDS; Testpoint

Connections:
+15V: D1.1 (K), D3.1 (K), J1.1, R2.1
/PWM_A: D3.2 (A), D4.1 (K), J2.3, T1.1 (AA)
/PWM_B: D1.2 (A), D2.1 (K), J2.1, T1.2 (AB)
Earth: Q1.3 (E), Q2.3 (S), R1.2, T1.3 (SA), TP2.1
GND: D2.2 (A), D4.2 (A), J1.2, J2.2
unnamed: JP1.1, JP3.1, R1.1, T1.4 (SB), TP1.1
unnamed: JP1.2, Q1.1 (G)
unnamed: JP2.1, Q1.2 (C)
unnamed: JP2.2, R2.2, TP3.1
unnamed: JP2.3, Q2.1 (D)
unnamed: JP3.2, Q2.2 (G)

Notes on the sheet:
unir masas

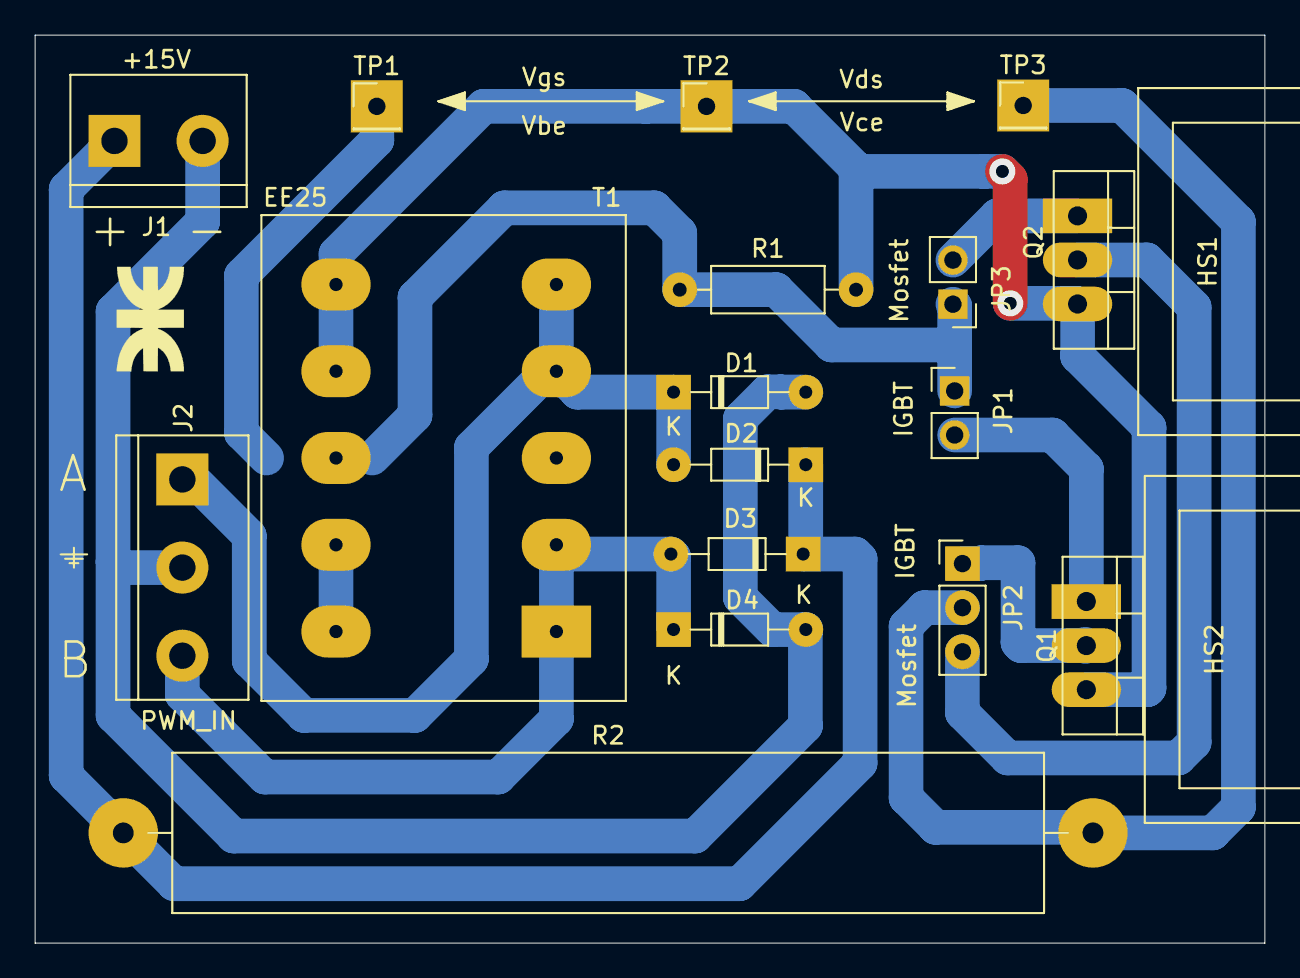
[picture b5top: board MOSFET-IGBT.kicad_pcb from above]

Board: 2 copper layers, 70.9 x 52.3 mm, 20 parts (0 on the bottom side), 11 nets.
